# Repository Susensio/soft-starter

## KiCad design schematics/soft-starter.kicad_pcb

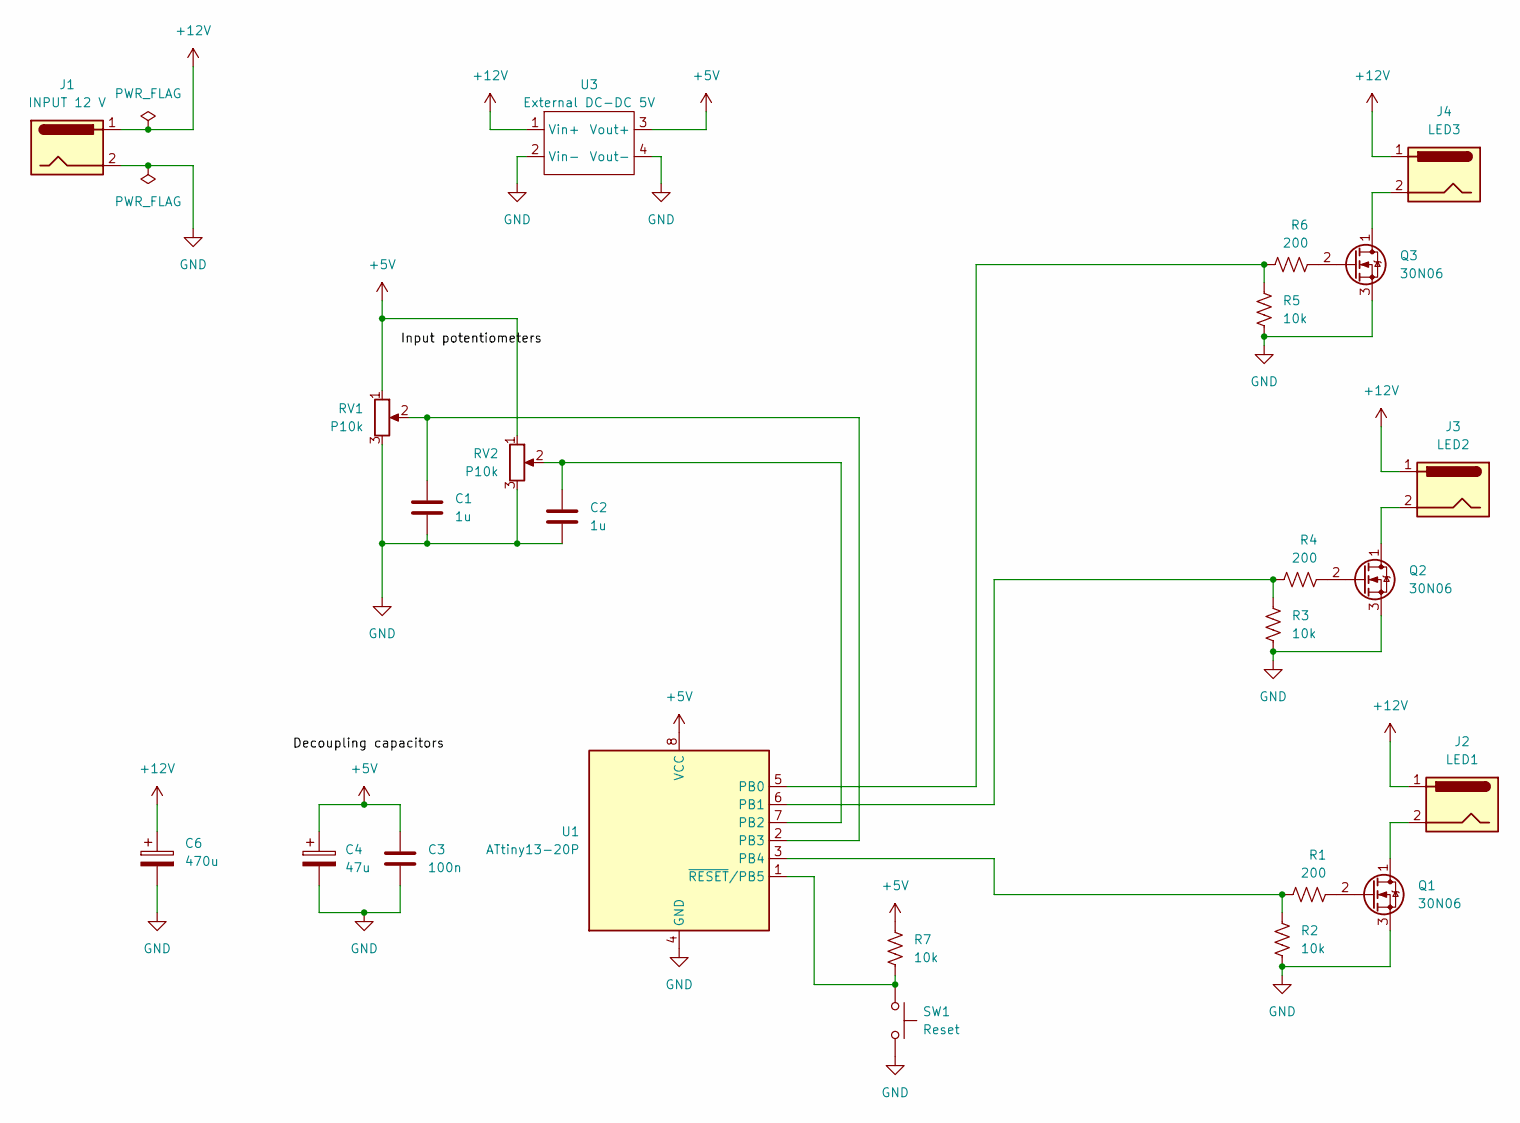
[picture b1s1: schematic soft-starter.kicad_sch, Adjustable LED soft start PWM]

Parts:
C1, C2: 1u; C_Radial_D4.0mm_H7.0mm_P1.50mm
C3: 100n; C_Disc_D5.0mm_W2.5mm_P2.50mm
C4: 47u; CP_Axial_L11.0mm_D5.0mm_P18.00mm_Horizontal
C6: 470u; CP_Radial_D8.0mm_P5.00mm
J1: INPUT 12 V; TerminalBlock_bornier-2_P5.08mm
J2: LED1; TerminalBlock_TE_282834-2_1x02_P2.54mm_Horizontal
J3: LED2; TerminalBlock_TE_282834-2_1x02_P2.54mm_Horizontal
J4: LED3; TerminalBlock_TE_282834-2_1x02_P2.54mm_Horizontal
Q1, Q2, Q3: 30N06; DirectFET_MD
R1, R4, R6: 200; R_Axial_DIN0207_L6.3mm_D2.5mm_P10.16mm_Horizontal
R2, R3, R5, R7: 10k; R_Axial_DIN0207_L6.3mm_D2.5mm_P10.16mm_Horizontal
RV1, RV2: P10k; Potentiometer_Bourns_3296X_Horizontal
SW1: Reset; SW_PUSH_6mm
U1: ATtiny13-20P; DIP-8_W7.62mm
U3: External DC-DC 5V; 5V 3A BUCK ALIEXPRESS

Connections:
+5V: C3.1, C4.1, R7.1, RV1.1, RV2.1, U1.8 (VCC), U3.3 (Vout+)
+12V: C6.1, J1.1, J2.1, J3.1, J4.1, U3.1 (Vin+)
GND: C1.2, C2.2, C3.2, C4.2, C6.2, J1.2, Q1.3 (S), Q2.3 (S), Q3.3 (S), R2.2, R3.2, R5.2, RV1.3, RV2.3, SW1.2, U1.4 (GND), U3.2 (Vin-), U3.4 (Vout-)
unnamed: J2.2, Q1.1 (D)
unnamed: Q1.2 (G), R1.2
unnamed: J3.2, Q2.1 (D)
unnamed: Q2.2 (G), R4.2
unnamed: J4.2, Q3.1 (D)
unnamed: Q3.2 (G), R6.2
unnamed: R5.1, R6.1, U1.5 (PB0)
unnamed: R3.1, R4.1, U1.6 (PB1)
unnamed: C2.1, RV2.2, U1.7 (PB2)
unnamed: C1.1, RV1.2, U1.2 (PB3)
unnamed: R1.1, R2.1, U1.3 (PB4)
unnamed: R7.2, SW1.1, U1.1 (~RESET/PB5)

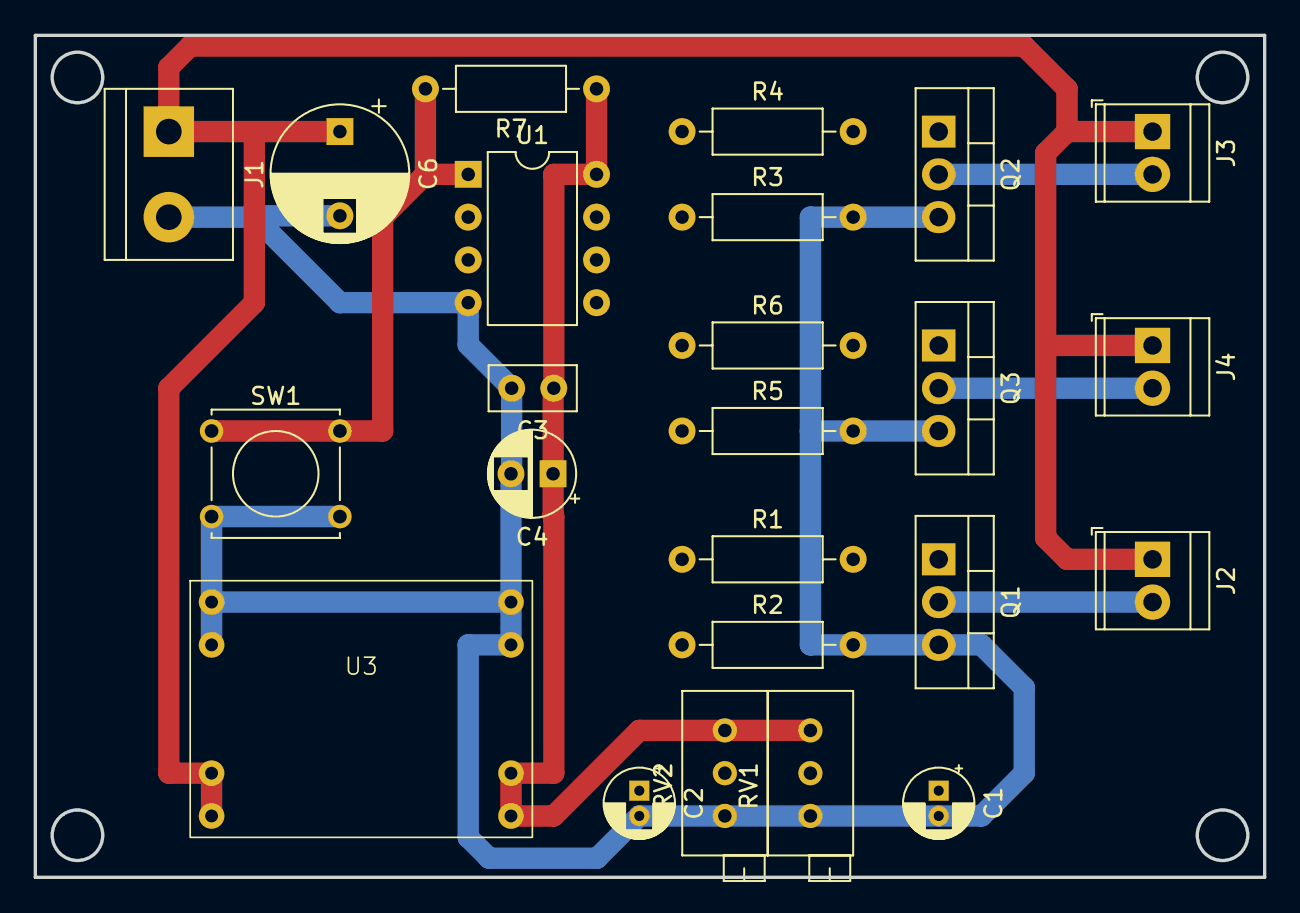
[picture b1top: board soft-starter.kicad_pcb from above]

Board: 6 copper layers, 73.0 x 50.0 mm, 24 parts (0 on the bottom side), 15 nets.

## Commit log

2024-04-19 Add arduino code
2024-04-19 Add gitignore
2024-04-19 Add kicad schematics
2024-04-19 Add docs and printed schematics
2024-04-22 Refactor src
2024-04-22 Update pcb to actual thing
2024-04-25 Add photos
2024-04-25 Add enclosure 3d print layout
2024-05-13 Fix flickering
